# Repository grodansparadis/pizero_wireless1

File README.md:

<h1>Pizero Wireless 1 HAT</h1>

The Pizero Wireless 1 HAT is a PCB module that can host either

<ul>
<li>One nrf24L10 wireless tranceiver.</li>
<li>One Microchip MV24J40A/B IEEE 802.11.14 tranceiver module.</li>
<li>One ESP8288 WiFi module.</li>
</ul>

You can order the module from the <a href="http://www.frogshop.se">FrogShop</a>.

<hr>

This project is licensed under the 
<a href="http://creativecommons.org/licenses/by-nc-sa/3.0/">Creative Commons open source license Attribution-NonCommercial-ShareAlike 3.0 Unported</a>. 
Other license options are available by conacting <a href="malto:info@grodansparadis.com">Paradis of the Frog AB</a>

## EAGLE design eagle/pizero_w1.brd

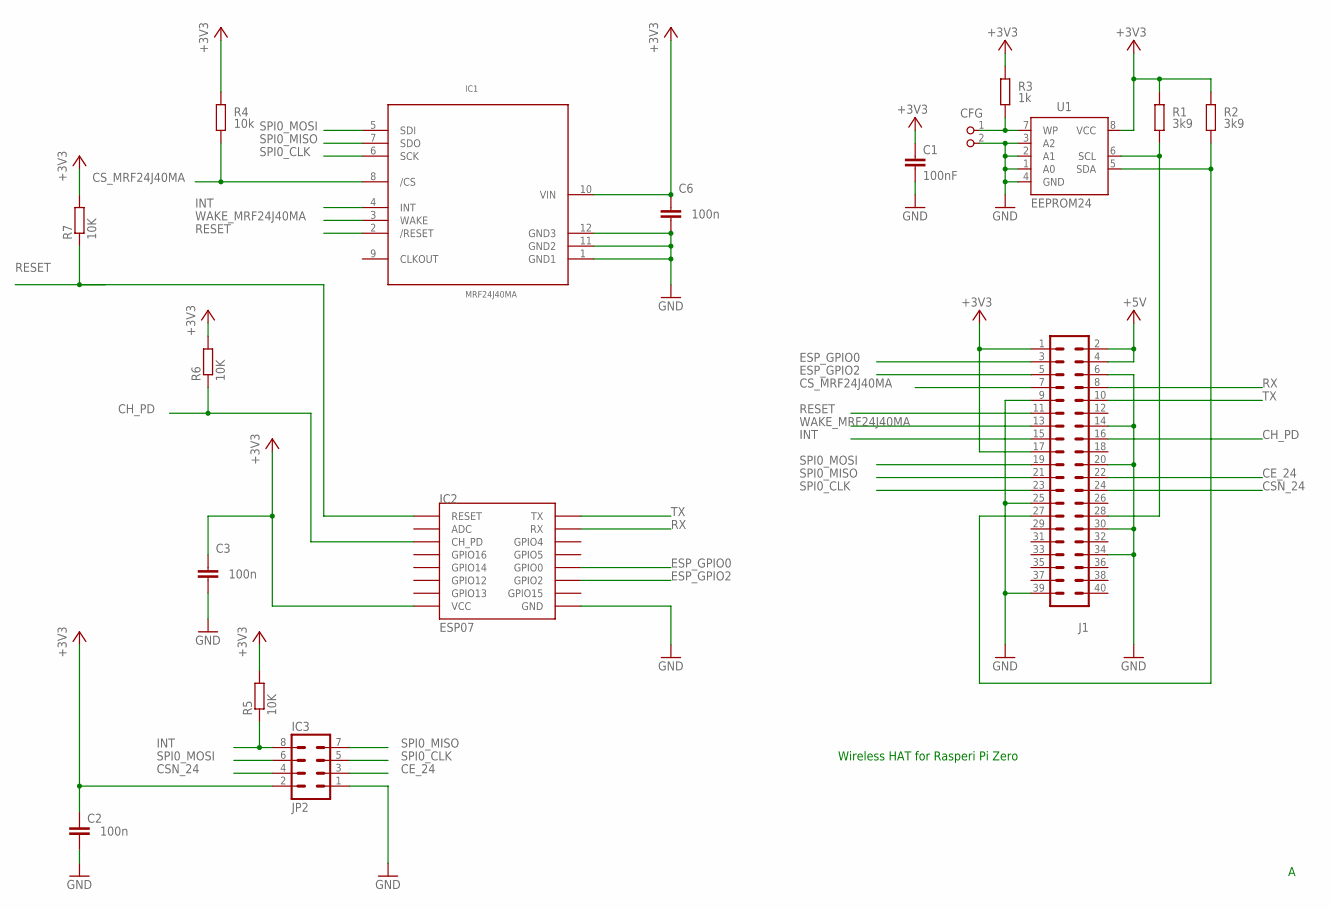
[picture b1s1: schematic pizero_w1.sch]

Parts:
C1: 100nF; C0805K
C2, C3, C6: 100n; C0805
CFG: PIN2_100; PIN_W_2
IC1: MRF24J40MA
IC2: ESP07; ESP12
IC3: JP2; MA04-2
J1: PIZERO_THROUGH_HOLE; PIZERO_THOUGH_HOLE
R1, R2: 3k9; M0805; TOLERANCE 5%
R3: 1k; M0805; TOLERANCE 5%
R4: 10k; M0805; TOLERANCE 5%
R5, R6, R7: 10K; R0805
U1: EEPROM24; SOIC8

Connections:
+3V3: C1.1, C2.1, C3.1, C6.1, IC1.10 (VIN), IC2.VCC, IC3.2, J1.1, J1.17, R1.2, R2.2, R3.2, R4.2, R5.2, R6.2, R7.2, U1.8 (VCC)
+5V: J1.2, J1.4
CE_24: IC3.3, J1.22
CH_PD: IC2.CH_PD, J1.16, R6.1
CSN_24: IC3.4, J1.24
CS_MRF24J40MA: IC1.8 (/CS), J1.7, R4.1
ESP_GPIO0: IC2.GPIO0, J1.3
ESP_GPIO2: IC2.GPIO2, J1.5
GND: C1.2, C2.2, C3.2, C6.2, CFG.2, IC1.1 (GND1), IC1.11 (GND2), IC1.12 (GND3), IC2.GND, IC3.1, J1.6, J1.9, J1.14, J1.20, J1.25, J1.30, J1.34, J1.39, U1.1 (A0), U1.2 (A1), U1.3 (A2), U1.4 (GND)
INT: IC1.4 (INT), IC3.8, J1.15, R5.1
unnamed: CFG.1, R3.1, U1.7 (WP)
RESET: IC1.2 (/RESET), IC2.RESET, J1.11, R7.1
RX: IC2.RX, J1.8
SCL: J1.28, R1.1, U1.6 (SCL)
SDA: J1.27, R2.1, U1.5 (SDA)
SPI0_CLK: IC1.6 (SCK), IC3.5, J1.23
SPI0_MISO: IC1.7 (SDO), IC3.7, J1.21
SPI0_MOSI: IC1.5 (SDI), IC3.6, J1.19
TX: IC2.TX, J1.10
WAKE_MRF24J40MA: IC1.3 (WAKE), J1.13

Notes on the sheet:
Wireless HAT for Rasperi Pi Zero

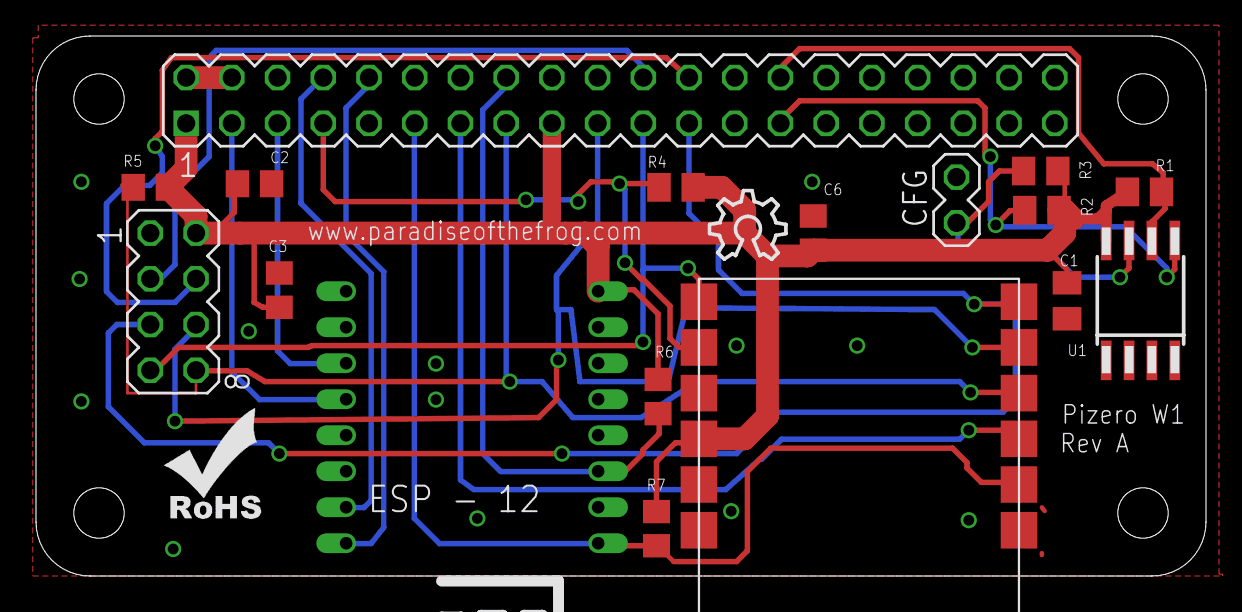
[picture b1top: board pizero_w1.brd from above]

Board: 2 copper layers, 65.0 x 30.0 mm, 19 parts (0 on the bottom side), 20 nets.

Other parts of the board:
U$1: OSHW_8X150_NOTEXT
U$2: ROHS_SILK

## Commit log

2015-12-06 Initial checkin
2015-12-06 Added pcb picture
2015-12-06 Edit
2015-12-17 added license
2016-10-14 Edited componet texts
